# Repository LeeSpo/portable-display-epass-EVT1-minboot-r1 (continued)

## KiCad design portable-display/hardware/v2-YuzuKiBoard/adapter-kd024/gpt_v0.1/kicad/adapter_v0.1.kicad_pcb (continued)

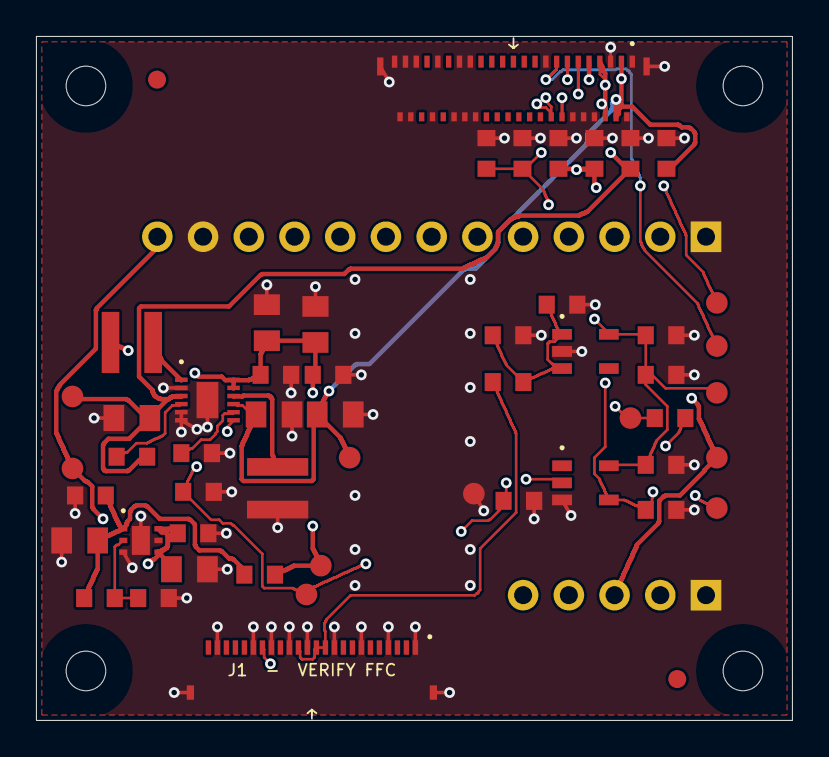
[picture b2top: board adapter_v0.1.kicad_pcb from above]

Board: 4 copper layers, 42.0 x 38.0 mm, 60 parts (0 on the bottom side), 25 nets.

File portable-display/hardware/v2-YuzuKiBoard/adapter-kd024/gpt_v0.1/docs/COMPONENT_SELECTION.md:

# 逐位号选型和采购状态

所有器件均为工程候选，不能按此表直接下单。资料索引见 SOURCES.md。仅指定 J2 的 LCSC 编号已核对，**全部基础／扩展库类别待确认**；无证据时不填写“基础库”。被动器件的 MPN、额定功率、有效电容和盘型兼容性尚未落实。

机械孔、光学定位点、裸铜测试点不是贴片采购元件，明确排除 BOM／CPL。H1/H2 手焊，R8 禁止默认装配，分别在 DNP 表列“不贴”。

| 位号 | 候选值／型号 | 选择理由 | LCSC／采购状态 | 库分类／装配 |
|---|---|---|---|---|
| J1 | FH34SRJ-24S-0.5SH(50) | 指定系列 24P 主板接口，自建专用焊盘；线缆面别待确认 [S4] | 待确认 MPN／LCSC 映射 | 待确认：基础／扩展库 |
| J2 | 502598-4593 | 指定 45P 0.3mm 触点、单双脚错列座；采用 C5365339，尾号相容性待确认 [S1,S10] | C5365339 | 待确认：基础／扩展库 |
| H1 | MANUAL: 1x13 pass-through | 13P 底向插合直通排母，Gerber 精确坐标；手焊料号／高度待确认 | 待确认 MPN／LCSC 映射 | 待确认：基础／扩展库 / 不贴（DNP） |
| H2 | MANUAL: 1x05 pass-through | 5P 底向插合直通排母，行距 19.913mm；手焊料号／高度待确认 | 待确认 MPN／LCSC 映射 | 待确认：基础／扩展库 / 不贴（DNP） |
| U1 | TPS65631DPDR | 保留指定 TPS65631；正负偏压，工作输入不能直接接 5V [S3] | 待确认 MPN／LCSC 映射 | 待确认：基础／扩展库 |
| U2 | TLV76701DRVR | 5V 前级降至标称 3.584V；DRV6 小型可调 LDO，热条件待验证 [S6] | 待确认 MPN／LCSC 映射 | 待确认：基础／扩展库 |
| U3 | TLV75518PDBVR | 仅从 J1 3V3 支路提供固定 1.8V，配输入／输出去耦 [S7] | 待确认 MPN／LCSC 映射 | 待确认：基础／扩展库 |
| U4 | SN74LVC1G17DBVR | 1.8V 供电、容忍 3.3V 输入的非反相施密特缓冲，含 Ioff，适配 RESX [S8] | 待确认 MPN／LCSC 映射 | 待确认：基础／扩展库 |
| L1 | 4.7uH XFL4020-472MEC | 4.7µH 升压电感；DCR／饱和电流／温升电流见电感预算，最坏峰值待验证 [S5] | 待确认 MPN／LCSC 映射 | 待确认：基础／扩展库 |
| L2 | 4.7uH XFL4020-472MEC | 4.7µH 反相电感，SWN 到 GND；同 L1 电流等级候选 [S5] | 待确认 MPN／LCSC 映射 | 待确认：基础／扩展库 |
| R1 | 0R 0603 | 0603 0Ω 偏压输入测流断点，不能以主板 3V3 绕过前级 | 待确认 MPN／LCSC 映射 | 待确认：基础／扩展库 |
| R2 | 0R 0603 | 0603 0Ω 逻辑 LDO 输入测流断点 | 待确认 MPN／LCSC 映射 | 待确认：基础／扩展库 |
| R3 | 34.8k 1% | 1% 34.8kΩ 反馈上臂，与 R4 产生标称 3.584V | 待确认 MPN／LCSC 映射 | 待确认：基础／扩展库 |
| R4 | 10k 1% | 1% 10kΩ 反馈下臂，控制前级电压 | 待确认 MPN／LCSC 映射 | 待确认：基础／扩展库 |
| R5 | 10k 1% | 指定 10kΩ CTRL 下拉，确保偏压默认关断 | 待确认 MPN／LCSC 映射 | 待确认：基础／扩展库 |
| R6 | 100k 1% | 100kΩ 复位输入下拉，无 FFC 时保持低态 | 待确认 MPN／LCSC 映射 | 待确认：基础／扩展库 |
| R7 | 100k 1% | 100kΩ 复位输出下拉，1.8V 时负载约 18µA | 待确认 MPN／LCSC 映射 | 待确认：基础／扩展库 |
| R8 | 0R DNP | SWIRE→CTRL 预留连接，默认不贴，避免未经确认的输出／时序冲突 | 待确认 MPN／LCSC 映射 | 待确认：基础／扩展库 / 不贴（DNP） |
| R9 | 0R 0603 Kelvin | 0603 0Ω Kelvin 采样连接，在 C9 正端取样，不在芯片旁草率并 FBS | 待确认 MPN／LCSC 映射 | 待确认：基础／扩展库 |
| C1 | 10uF 10V X7R | VBUS 5V 输入 10µF，10V X7R，满足耐压要求；需查偏压降容 | 待确认 MPN／LCSC 映射 | 待确认：基础／扩展库 |
| C2 | 0.1uF 10V X7R | U2 输入的 100nF 高频去耦，10V X7R | 待确认 MPN／LCSC 映射 | 待确认：基础／扩展库 |
| C3 | 10uF 10V X7R | U2 前级输出 10µF 储能，检查 LDO 稳定性和有效容值 | 待确认 MPN／LCSC 映射 | 待确认：基础／扩展库 |
| C4 | 0.1uF 10V X7R | U2 输出 100nF 高频去耦 | 待确认 MPN／LCSC 映射 | 待确认：基础／扩展库 |
| C5 | 10uF 10V X7R | TPS 输入 10µF 储能之一，与 C6 并联 [S3] | 待确认 MPN／LCSC 映射 | 待确认：基础／扩展库 |
| C6 | 10uF 10V X7R | TPS 输入 10µF 储能之二，按典型外围候选 [S3] | 待确认 MPN／LCSC 映射 | 待确认：基础／扩展库 |
| C7 | 0.1uF 10V X7R | TPS AVIN/PVIN 支路附近 100nF 去耦之一 | 待确认 MPN／LCSC 映射 | 待确认：基础／扩展库 |
| C8 | 0.1uF 10V X7R | TPS AVIN/PVIN 支路附近 100nF 去耦之二 | 待确认 MPN／LCSC 映射 | 待确认：基础／扩展库 |
| C9 | 10uF 10V X7R | ELVDD 输出 10µF，与 R9 形成反馈采样端 [S3] | 待确认 MPN／LCSC 映射 | 待确认：基础／扩展库 |
| C10 | 10uF 10V X7R | ELVSS 输出 10µF 之一，X7R 无极性 [S3] | 待确认 MPN／LCSC 映射 | 待确认：基础／扩展库 |
| C11 | 10uF 10V X7R | ELVSS 输出 10µF 之二，X7R 无极性 [S3] | 待确认 MPN／LCSC 映射 | 待确认：基础／扩展库 |
| C12 | 0.1uF 10V X7R | CT 100nF 时间设置候选，最终时序按手册和屏厂确认 [S3] | 待确认 MPN／LCSC 映射 | 待确认：基础／扩展库 |
| C13 | 4.7uF 10V X7R | U3 输入 4.7µF 储能，降低线缆供电扰动 | 待确认 MPN／LCSC 映射 | 待确认：基础／扩展库 |
| C14 | 0.1uF 10V X7R | U3 输入 100nF 去耦 | 待确认 MPN／LCSC 映射 | 待确认：基础／扩展库 |
| C15 | 4.7uF 10V X7R | U3 输出 4.7µF，维持逻辑电源并核对稳定性 [S7] | 待确认 MPN／LCSC 映射 | 待确认：基础／扩展库 |
| C16 | 0.1uF 10V X7R | 1.8V LDO 输出 100nF 去耦 | 待确认 MPN／LCSC 映射 | 待确认：基础／扩展库 |
| C17 | 0.1uF 10V X7R | U4 供电脚 100nF 去耦 | 待确认 MPN／LCSC 映射 | 待确认：基础／扩展库 |
| C18 | 1uF 10V X7R | 屏 VCI 就地 1µF 储能 | 待确认 MPN／LCSC 映射 | 待确认：基础／扩展库 |
| C19 | 0.1uF 10V X7R | 屏 VCI 就地 100nF 去耦 | 待确认 MPN／LCSC 映射 | 待确认：基础／扩展库 |
| C20 | 1uF 10V X7R | 屏 VDDIO 就地 1µF 储能 | 待确认 MPN／LCSC 映射 | 待确认：基础／扩展库 |
| C21 | 0.1uF 10V X7R | 屏 VDDIO 就地 100nF 去耦 | 待确认 MPN／LCSC 映射 | 待确认：基础／扩展库 |
| C22 | 1uF 10V X7R | 屏 ELVDD 就地 1µF，须核对有效电容和电流冲击 | 待确认 MPN／LCSC 映射 | 待确认：基础／扩展库 |
| C23 | 1uF 10V X7R | 屏 ELVSS 就地 1µF，无极性 MLCC | 待确认 MPN／LCSC 映射 | 待确认：基础／扩展库 |
| TP1 | VBUS_5V | 5V 输入探测，裸铜不贴装 | - | PCB 图形，非采购料 |
| TP2 | BIAS_IN_3V6 | TPS 输入探测，裸铜不贴装 | - | PCB 图形，非采购料 |
| TP3 | ELVDD | ELVDD 探测，未批准前不得带屏使能 | - | PCB 图形，非采购料 |
| TP4 | ELVSS | ELVSS 探测，未批准前不得带屏使能 | - | PCB 图形，非采购料 |
| TP5 | VDDIO_1V8 | 1.8V 逻辑电源探测 | - | PCB 图形，非采购料 |
| TP6 | PANEL_VCI_3V3 | H2-3／屏 VCI 3V3 探测 | - | PCB 图形，非采购料 |
| TP7 | LCD_EN | LCD_EN 控制／观察点，10kΩ 默认下拉 | - | PCB 图形，非采购料 |
| TP8 | PANEL_TE1 | 屏 TE1 输出观察，默认不外部驱动 | - | PCB 图形，非采购料 |
| TP9 | PANEL_TE | 屏 TE 输出观察，默认不外部驱动 | - | PCB 图形，非采购料 |
| TP10 | PANEL_SWIRE | 屏 SWIRE 输出观察；R8 默认不贴 | - | PCB 图形，非采购料 |
| TP11 | PANEL_RESET_1V8 | 屏侧 1.8V 复位观察 | - | PCB 图形，非采购料 |
| TP12 | GND | 仪器地参考 | - | PCB 图形，非采购料 |
| MH1 | M2 NPTH 2.2 | 安装孔／定位点／裸铜测试特征，按任务尺寸，非器件 | - | PCB 图形，非采购料 |
| MH2 | M2 NPTH 2.2 | 安装孔／定位点／裸铜测试特征，按任务尺寸，非器件 | - | PCB 图形，非采购料 |
| MH3 | M2 NPTH 2.2 | 安装孔／定位点／裸铜测试特征，按任务尺寸，非器件 | - | PCB 图形，非采购料 |
| MH4 | M2 NPTH 2.2 | 安装孔／定位点／裸铜测试特征，按任务尺寸，非器件 | - | PCB 图形，非采购料 |
| FID1 | FID 1mm / 2mm mask | 安装孔／定位点／裸铜测试特征，按任务尺寸，非器件 | - | PCB 图形，非采购料 |
| FID2 | FID 1mm / 2mm mask | 安装孔／定位点／裸铜测试特征，按任务尺寸，非器件 | - | PCB 图形，非采购料 |

采购签核必须逐项补全具体 MPN、LCSC、基础／扩展库及替代规则。所有 10V X7R 值均为候选规格，不能在未检查 DC 偏压曲线时以名义容量作为稳定性证明。所有 0Ω 测流位要核对额定电流，R3/R4 要核对电压误差预算；没有据此表自动放行的权限。
